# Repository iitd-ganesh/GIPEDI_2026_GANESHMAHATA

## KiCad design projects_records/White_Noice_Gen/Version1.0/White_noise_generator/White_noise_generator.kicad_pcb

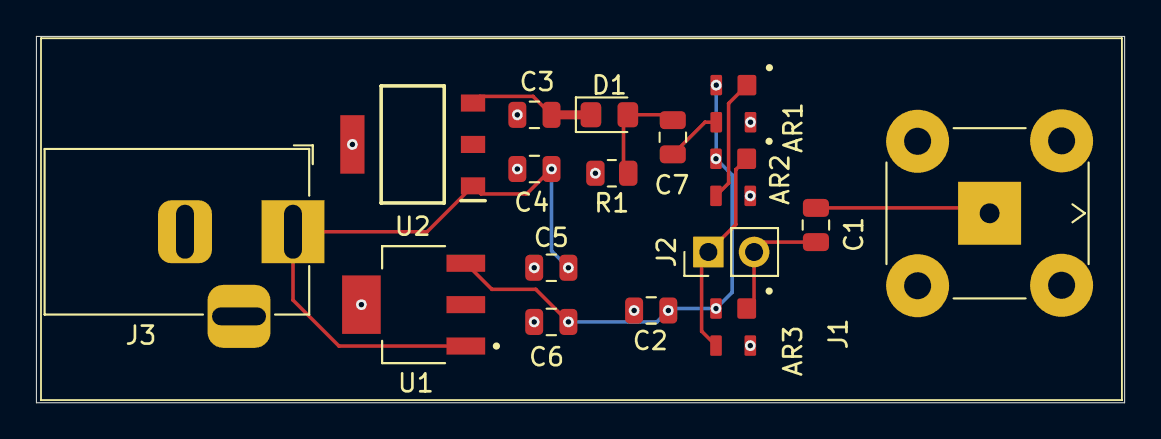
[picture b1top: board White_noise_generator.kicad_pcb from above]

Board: 2 copper layers, 60.5 x 20.3 mm, 17 parts (0 on the bottom side), 10 nets.

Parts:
AR1, AR2, AR3: MAX2650; SOT190P228X119-4N-ADITYA
C1, C7: 470pF; C_0805_2012Metric
C2: 0.1uF; C_0805_2012Metric
C3, C6: 22uF; C_0805_2012Metric
C4, C5: 0.47uF; C_0805_2012Metric
D1: D_Zener; D_0805_2012Metric_Pad1.15x1.40mm_HandSolder
J1: Conn_Coaxial; BNC_WNG1
J2: Conn_01x02_Pin; PinHeader_1x02_P2.54mm_Vertical
J3: Barrel_Jack; BarrelJack_Horizontal
R1: 30; R_0805_2012Metric
U1: LM2940IMP-9.0_NOPB; SOT230P700X180-4N
U2: LM2940CSX-15_NOPB; SOT230P700X180-4N

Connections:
+5V: AR1.2 (VCC), AR2.2 (VCC), AR3.2 (VCC), C2.1, C6.2, U1.3 (OUT)
+14V: C3.2, D1.1 (K), U2.3 (OUT)
GND: AR1.4 (GND), AR2.4 (GND), AR3.4 (GND), C2.2, C3.1, C4.1, C5.1, C6.1, J1.2 (Ext), J3.2, R1.2, U1.4 (GND), U2.4 (GND_2)
unnamed: AR1.3 (IN), C7.2
unnamed: AR1.1 (OUT), AR2.3 (IN)
unnamed: AR2.1 (OUT), AR3.3 (IN), J2.1
unnamed: AR3.1 (OUT), C1.1, J2.2
unnamed: C7.1, D1.2 (A), R1.1
unnamed: C1.2, J1.1 (In)
VIN: C4.2, C5.2, J3.1, U1.1 (IN), U2.1 (IN)

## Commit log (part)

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2026-05-19 Exp-0 and Exp-1 added
2026-05-19 testing
2026-05-19 testing step 2
2026-05-19 testing part 3
2026-05-19 testing part 4
2026-05-19 update task 2
2026-05-19 code for this
2026-05-19 .hex file update
2026-05-19 report.md file updated
2026-05-19 lib included
2026-05-19 png_wheather added
2026-05-20 commit backlog
2026-05-20 png updated in calc
2026-05-20 exp 3 added
2026-05-20 uploaded lib.zip
2026-05-20 Rename zip file
2026-05-20 .md EXP-1:smart fixed
2026-05-21 exp-4 updated
2026-05-21 all commited exp 2
2026-05-21 del freq
2026-05-21 exp4-motor on off
2026-05-21 done for exp 4
2026-05-21 exp-4 update
2026-05-21 temp_recorder
2026-05-21 update all deleted file
2026-05-22 wheather forecasting
2026-05-22 All report converted to pdf
2026-05-22 new file created
2026-05-22 combine report
2026-05-22 readme.pdf
2026-05-27 calculator update
2026-05-27 Exp-3 Updates -Report and pngs
2026-05-27 digilock arduino file update
2026-06-01 final report of all 4 exp updated
2026-06-08 Incomplete Exp-3-Gofurthur-2
2026-06-08 Comment added till exp-1 completed
2026-06-08 report -image dir cng
2026-06-12 Jun 12, 2026, 7:59 AM
2026-06-12 Jun 12, 2026, 8:01 AM
2026-06-12 Jun 12, 2026, 8:02 AM
2026-06-12 Jun 12, 2026, 2:36 PM
2026-06-12 Jun 12, 2026, 2:44 PM
2026-06-15 Jun 15, 2026, 9:57 AM
2026-06-15 Jun 15, 2026, 10:03 AM
2026-06-15 Jun 15, 2026, 10:08 AM
2026-06-15 Jun 15, 2026, 10:16 AM
2026-06-15 Jun 15, 2026, 11:14 AM
2026-06-15 test
2026-06-17 16.06.2026
2026-06-23 load cell record updated
2026-06-29 Jun 29, 2026, 3:43 PM
2026-06-30 Jun 30, 2026, 11:00 AM
2026-06-30 Jun 30, 2026, 11:02 AM
2026-06-30 Jun 30, 2026, 11:03 AM
2026-06-30 Jun 30, 2026, 4:39 PM
